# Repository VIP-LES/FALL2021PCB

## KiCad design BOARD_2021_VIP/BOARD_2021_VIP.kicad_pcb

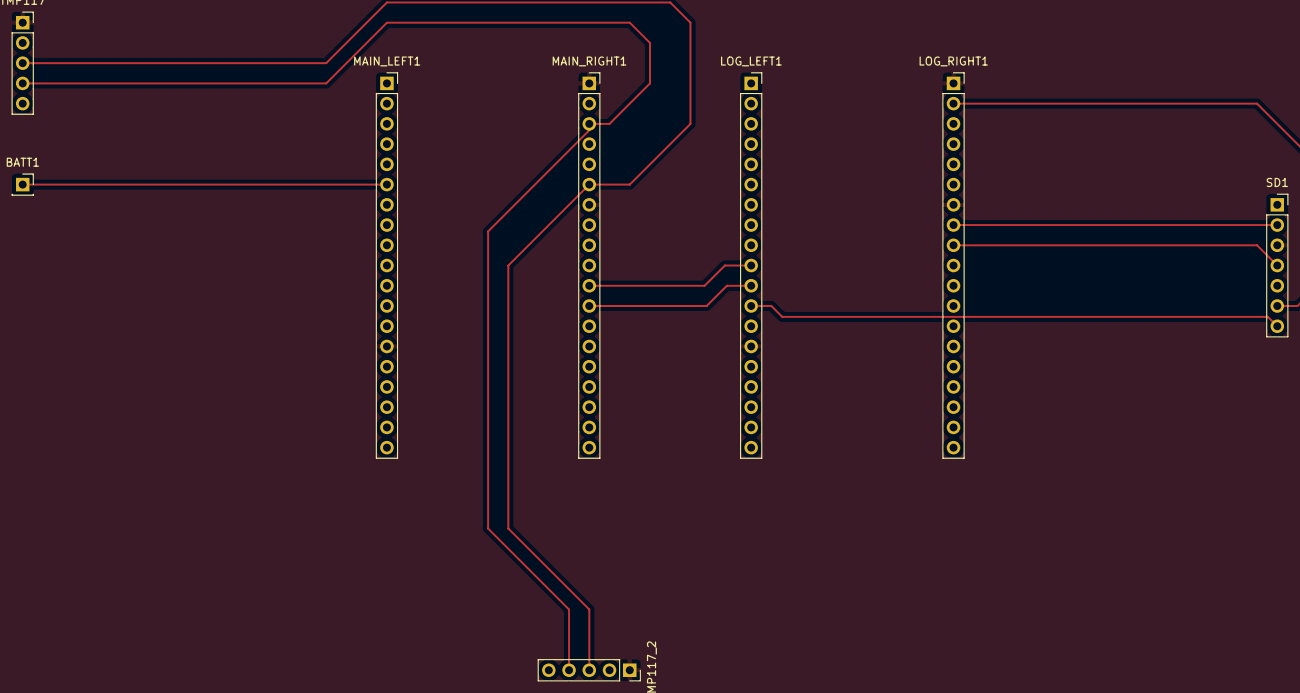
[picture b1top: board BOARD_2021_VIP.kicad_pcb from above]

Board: 2 copper layers, 8 parts (0 on the bottom side), 11 nets.

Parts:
BATT1: Conn_01x01; PinSocket_1x01_P2.54mm_Vertical
LOG_LEFT1: Conn_01x19; PinSocket_1x19_P2.54mm_Vertical
LOG_RIGHT1: Conn_01x19; PinSocket_1x19_P2.54mm_Vertical
MAIN_LEFT1: Conn_01x19; PinSocket_1x19_P2.54mm_Vertical
MAIN_RIGHT1: Conn_01x19; PinSocket_1x19_P2.54mm_Vertical
SD1: Conn_01x07; PinSocket_1x07_P2.54mm_Vertical
TMP117, TMP117_2: Conn_01x05; PinSocket_1x05_P2.54mm_Vertical

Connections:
3V3: LOG_LEFT1.1, MAIN_LEFT1.1, SD1.5, TMP117.2, TMP117_2.2
14_2: LOG_LEFT1.12, SD1.7
16: LOG_LEFT1.11, MAIN_RIGHT1.12
17: LOG_LEFT1.10, MAIN_RIGHT1.11
18_2: LOG_RIGHT1.9, SD1.4
19_2: LOG_RIGHT1.8, SD1.2
21: MAIN_RIGHT1.6, TMP117.3, TMP117_2.3
22: MAIN_RIGHT1.3, TMP117.4, TMP117_2.4
23_2: LOG_RIGHT1.2, SD1.6
35: BATT1.1, MAIN_LEFT1.6
GND: LOG_LEFT1.14, LOG_RIGHT1.1, LOG_RIGHT1.7, MAIN_LEFT1.14, MAIN_RIGHT1.1, MAIN_RIGHT1.7, SD1.3, TMP117.1, TMP117_2.1

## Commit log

2021-10-05 Added all relevant files
